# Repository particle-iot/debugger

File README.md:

# Particle debugger

**Design files for the CMSIS-DAP debugger**

The Particle Debugger gives you the power of professional debugging at a fraction of the cost. Using this accessory, you’ll be able to program Particle mesh-ready hardware over common interfaces like JTAG and SWD, using open source tools like GDB and openocd.

Supports the open source [CMSIS-DAP specification](https://os.mbed.com/handbook/DAPLink) and DAPLink firmware developed by ARM. On Mac, Linux, and Windows it requires no additional device drivers. 

It also provides a USB to TTL serial port. This requires no device drivers on Mac, Linux, or Windows 10 or later, but you may need to [install a device driver](https://os.mbed.com/docs/v5.9/tutorials/windows-serial-driver.html) for earlier versions of Windows to use the serial port feature.

Comes with one JTAG ribbon cable.

For more information about debugging see the [JTAG FAQ](https://docs.particle.io/support/particle-tools-faq/jtag/). Future version of Particle Workbench will support the Particle Debugger as well.

### Debugging mesh devices

Connecting a Argon, Boron, or Xenon to the debugger is as easy as connecting the included ribbon cable, as pictured below. It's keyed so it will only go in one way. The devices ship with a small plastic protective plug in the debugging connector; make sure you remove that first.

### Debugging legacy platforms

Using the headers on the Particle Debugger you can attach it to other ARM processor devices like the STM32 in the Particle Photon, P1, Electron, and E Series for SWD (serial wire debug).

With the debugger positioned like this, USB connector toward you and the headers facing up:

| Left Header | Right Header |
| --- | ----- |
| VDD | SWCLK |
| RTS | SWDIO |
| RX  | NC    |
| TX  | NC    |  
| CTS | GND   | 
| GND | VUSB  |

In order to use SWD debugging you need to connect:

- D7: SWDIO
- D6: SWCLK
- GND

## Connector

If you want to include the 5x2 micro JTAG connector on your own board a connector compatible with this one works:
 
- Connector Header Surface Mount 10 position 5x2 0.050" (1.27mm)
- [Samtec FTSH-105-01-F-DV-K](https://www.digikey.com/product-detail/en/FTSH-105-01-F-DV-K/SAM8796-ND/2649974)

In the connector directory is:

- JTAGConn.lbr, an Eagle CAD library file containing this connector footprint, symbol, and device. The device has all of the pins labeled for easy use.
- JTAGTest1.brd and .sch. This is just a simple breakout and is what I used to test the footprint. It works.

## Firmware Update

To update the interface firmware with the latest version:

1. Download the latest interface firmware from the firmware directory, above.
2. Press and hold the button on the Debugger.
3. Plug into an USB port of your PC.
4. It will show up a `MAINTENANCE` drive/volume.
5. Drag and drop the firmware to the drive/volume.
6. After that, it will be unmounted and remounted automatically and showing a `DAPLink` drive/volume.
7. Now, you can drag and drop any nRF52840 firmware into the `DAPLink` drive/volume to test.

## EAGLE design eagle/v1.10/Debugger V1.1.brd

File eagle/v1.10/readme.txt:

2021/5/7
1.change U$1 to be closed so the RESET pin is actually connected to the debug port.
2.expose SWO and /RESET on the 2 empty breakout header pins.

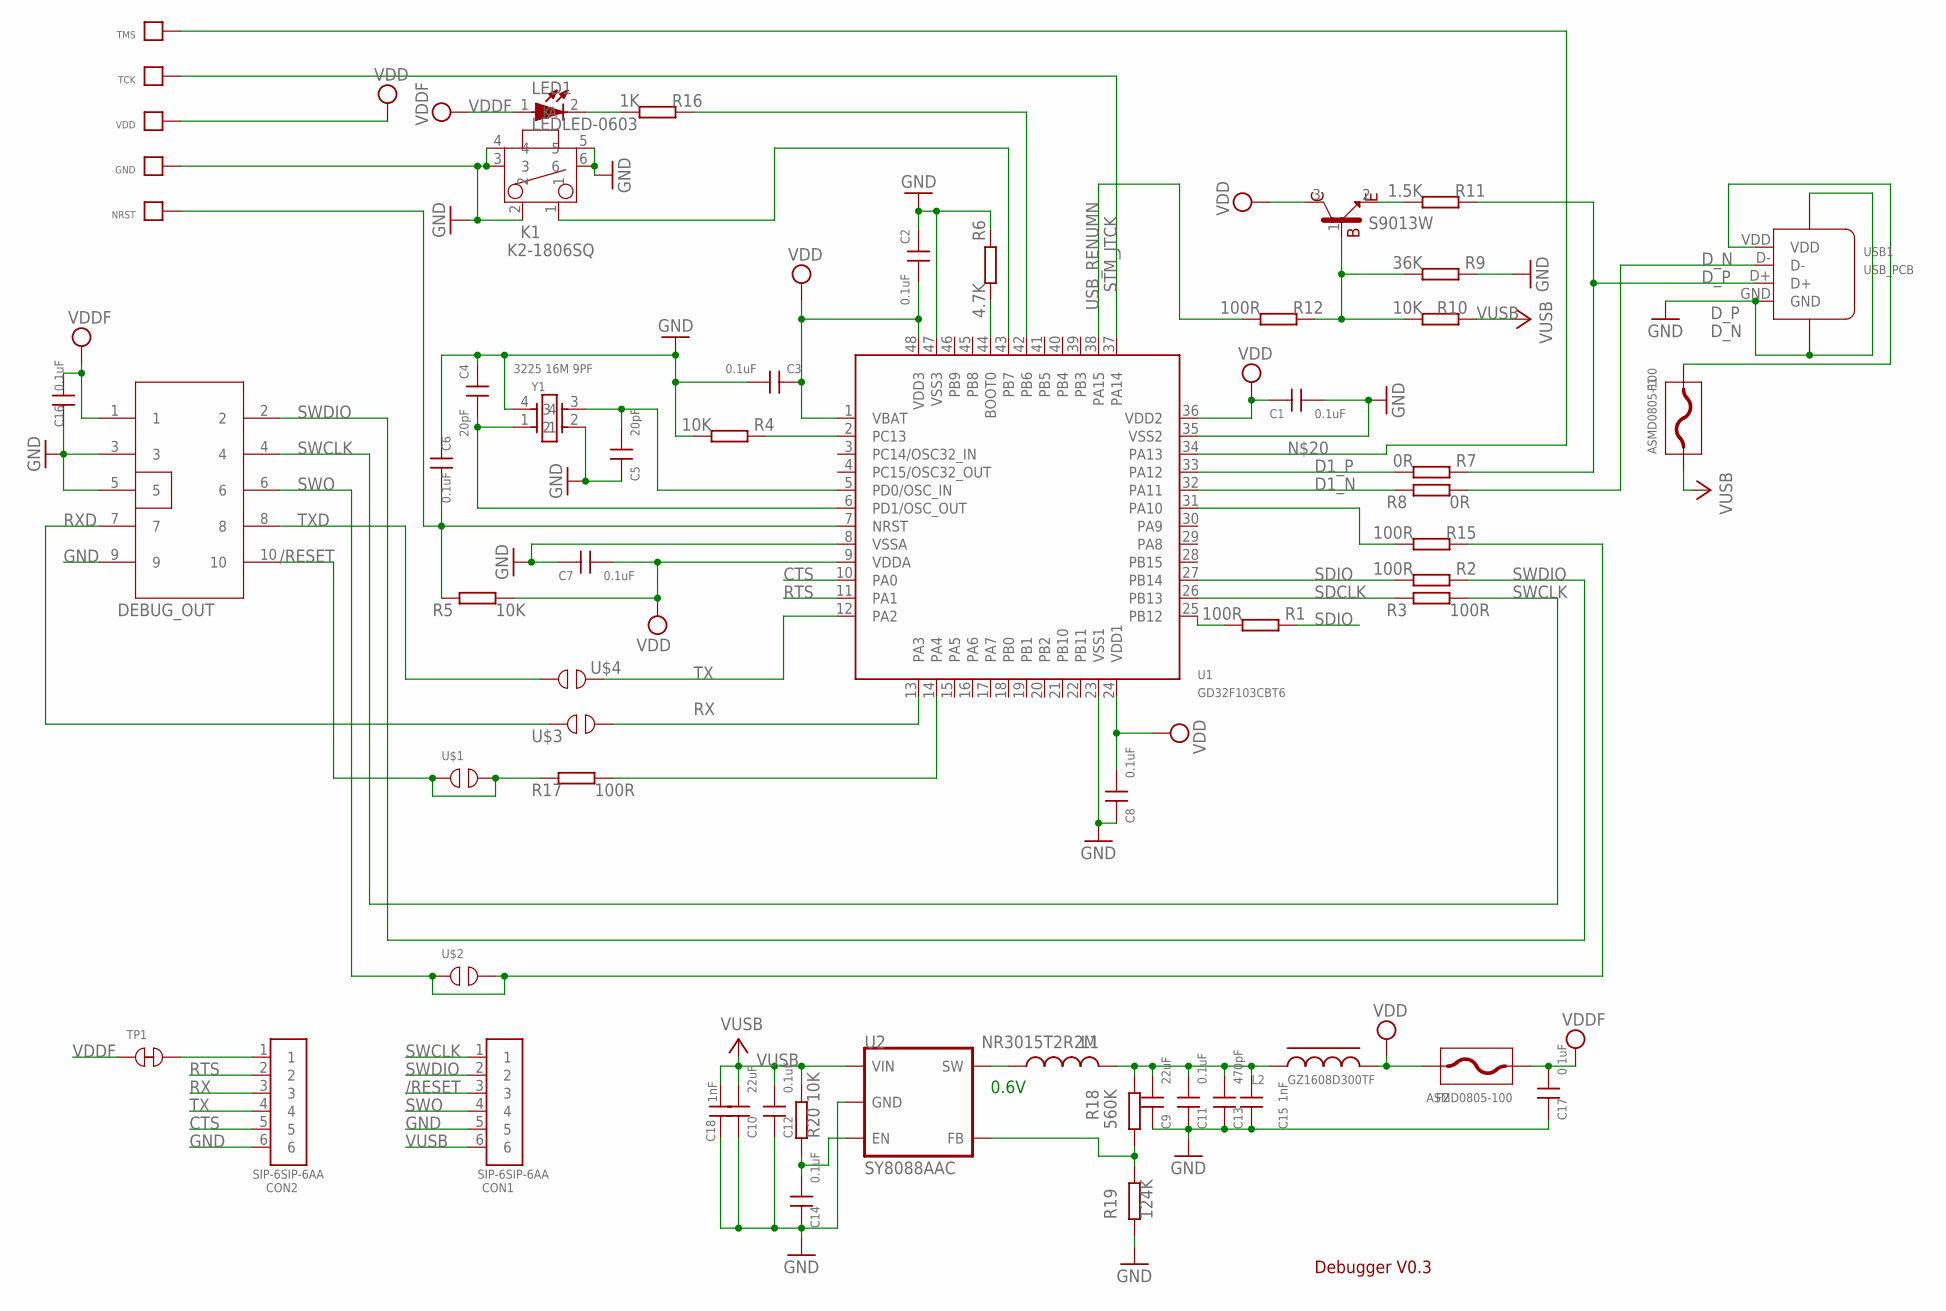
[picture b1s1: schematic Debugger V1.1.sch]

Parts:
C1, C2, C3, C6, C7, C8, C11, C12, C14, C16, C17: 0.1uF; C0402
C4, C5: 20pF; C0402
C9, C10: 22uF; C0805
C13: 470pF; C0402
C15, C18: 1nF; C0402
CON1, CON2: SIP-6SIP-6AA; PAIZHEN6P_2.54AA
DEBUG_OUT: CON5X2; CON5X2_1.27
F1, F2: ASMD0805-100; F0805
GND: TPTP; TP
K1: K2-1806SQ; K2-1806C
L1: NR3015T2R2M; INDUCTOR-NR3015
L2: GZ1608D300TF; R-0603A
LED1: LEDLED-0603; LED-0603
NRST: TPTP; TP
Q1: S9013W; SOT-323
R1, R2, R3, R12, R15, R17: 100R; R-0402S
R4, R5, R10, R20: 10K; R-0402S
R6: 4.7K; R-0402S
R7, R8: 0R; R-0402S
R9: 36K; R-0402S
R11: 1.5K; R-0402S
R16: 1K; R-0402S
R18: 560K; R-0402S
R19: 124K; R-0402S
TCK: TPTP; TP
TMS: TPTP; TP
TP1: TP_SHORT
U1: GD32F103CBT6; LQFP-48-7X7
U2: SY8088AAC; SOT23-5L
U$1, U$2, U$3, U$4: TP_OPEN
USB1: USB_PCB
VDD: TPTP; TP
Y1: 3225 16M 9PF; CRY_3225_SMT

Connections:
/RESET: CON1.3, DEBUG_OUT.10, R17.1, U$1.1, U$1.2
CTS: CON2.5, U1.10 (PA0)
D1_N: R8.1, U1.32 (PA11)
D1_P: R7.2, U1.33 (PA12)
D_N: R8.2, USB1.D-
D_P: R7.1, R11.1, USB1.D+
GND: C1.1, C2.2, C3.1, C4.2, C5.2, C6.2, C7.2, C8.2, C9.2, C10.2, C11.2, C12.2, C13.2, C14.2, C15.2, C16.2, C17.2, C18.2, CON1.5, CON2.6, DEBUG_OUT.3, DEBUG_OUT.5, DEBUG_OUT.9, GND.P$1, K1.2, K1.3, K1.4, K1.5, K1.6, R4.2, R6.1, R9.1, R19.1, U1.8 (VSSA), U1.23 (VSS1), U1.35 (VSS2), U1.47 (VSS3), U2.2 (GND), USB1.GND, USB1.GND1, USB1.GND2, Y1.2, Y1.4
unnamed: R1.2, U1.25 (PB12)
unnamed: C6.1, NRST.P$1, R5.1, U1.7 (NRST)
unnamed: R4.1, U1.2 (PC13)
unnamed: C5.1, U1.5 (PD0/OSC_IN), Y1.3
unnamed: C4.1, U1.6 (PD1/OSC_OUT), Y1.1
unnamed: Q1.1 (B), R9.2, R10.2, R12.1
unnamed: R15.2, U1.31 (PA10)
unnamed: Q1.2 (E), R11.2
unnamed: R6.2, U1.44 (BOOT0)
unnamed: LED1.2 (K), R16.2
unnamed: F1.P$2 (2), USB1.VDD
unnamed: K1.1, U1.43 (PB7)
unnamed: R16.1, U1.42 (PB6)
unnamed: L1.1, U2.3 (SW)
unnamed: R17.2, U1.14 (PA4)
unnamed: TMS.P$1, U1.34 (PA13)
unnamed: R18.1, R19.2, U2.5 (FB)
unnamed: C14.1, R20.1, U2.1 (EN)
unnamed: C9.1, C11.1, C13.1, C15.1, L1.2, L2.1, R18.2
RTS: CON2.2, U1.11 (PA1)
RX: CON2.3, U1.13 (PA3), U$3.2
RXD: DEBUG_OUT.7, U$3.1
SDCLK: R3.1, U1.26 (PB13)
SDIO: R1.1, R2.2, U1.27 (PB14)
STM_JTCK: TCK.P$1, U1.37 (PA14)
SWCLK: CON1.1, DEBUG_OUT.4, R3.2
SWDIO: CON1.2, DEBUG_OUT.2, R2.1
SWO: CON1.4, DEBUG_OUT.6, R15.1, U$2.1, U$2.2
TX: CON2.4, U1.12 (PA2), U$4.1
TXD: DEBUG_OUT.8, U$4.2
USB_RENUMN: R12.2, U1.38 (PA15)
VDD: C1.2, C2.1, C3.2, C7.1, C8.1, F2.P$2 (2), L2.2, Q1.3 (C), R5.2, U1.1 (VBAT), U1.9 (VDDA), U1.24 (VDD1), U1.36 (VDD2), U1.48 (VDD3), VDD.P$1
VDDF: C16.1, C17.1, CON2.1, DEBUG_OUT.1, F2.P$1 (1), LED1.1 (A), TP1.1, TP1.2
VUSB: C10.1, C12.1, C18.1, CON1.6, F1.P$1 (1), R10.1, R20.2, U2.4 (VIN)

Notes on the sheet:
0.6V
Debugger V0.3

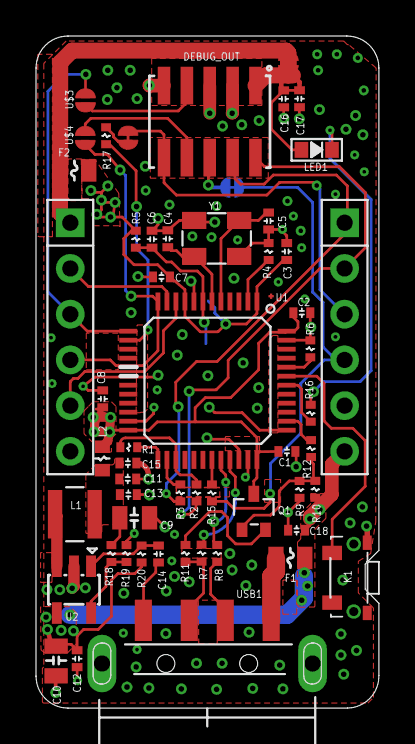
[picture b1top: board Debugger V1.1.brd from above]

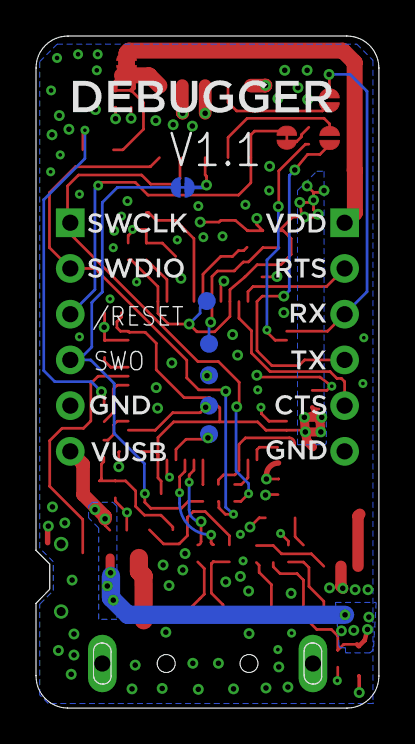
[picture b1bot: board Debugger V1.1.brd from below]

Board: 2 copper layers, 19.0 x 37.3 mm, 62 parts (7 on the bottom side), 41 nets.

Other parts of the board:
U$5, U$6: SPARK_LOGO2

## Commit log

2019-02-04 Public release
2019-02-04 Fix docs link
2019-02-04 Update link to firmware
2019-02-04 Add missing brd and pdf
2019-02-06 Add connector info
2021-05-14 create V1.1 file
